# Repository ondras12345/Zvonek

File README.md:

# Zvonek
A simple circuit for ringing a doorbell by briefly pressing a light switch.

The PCB was designed in EAGLE. It was milled out using a CNC. Because I needed
the PCB to be as small as possible, I had to place some of the components
outside the 1.27mm grid.

A fuse (not shown in the schematic) should be placed in series with the 12V
power line.

## Operation
The circuit is connected to a regular light switch, so that the neon lamp is
lit when the light is lit. The neon lamp is pointed at a LDR, thus forming
an optocoupler. A piece of heatshrink tubing is put over this assembly to
isolate it from ambient light.

The circuit is powered from the 12V DC bell power supply and is isolated from
the mains.

When the light is lit, a timer (about 2 s) starts. If the timer has not
finished yet and the light is already switched off, a MOSFET turns on and
the bell sounds.

```
       1   +-----------+           +---+
switch     |           |           |   |
       0 --+           +-----------+   +-------

       1   +------+                +------+
timer      |      |                |      |
       0 --+      +----------------+      +----

       1                               +---+
bell                                   |   |
       0 ------------------------------+   +---
```

This circuit should not be used with regular light bulbs, because the brief
switch-ons would reduce their lifespan. An LED light should be used instead.

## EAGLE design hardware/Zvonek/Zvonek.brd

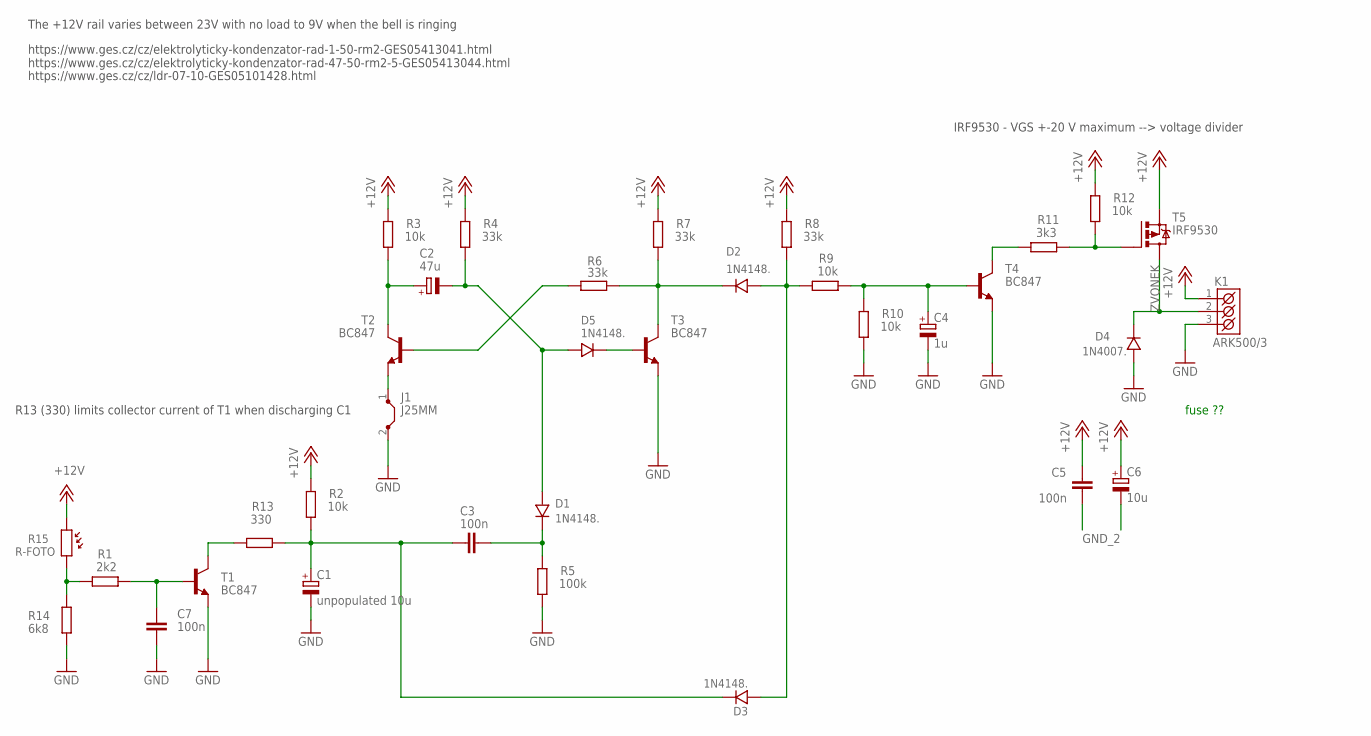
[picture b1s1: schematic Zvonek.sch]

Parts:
C1: unpopulated 10u; E2,5-5
C2: 47u; E2,5-6
C3, C5, C7: 100n; C1206
C4: 1u; E2-5
C6: 10u; E2,5-5
D1, D2, D3, D5: 1N4148.; SOD-80
D4: 1N4007.; SM-1
J1: J25MM; 25
K1: ARK500/3
R1: 2k2; R1206
R2, R3, R9, R10, R12: 10k; R1206
R4, R6, R7, R8: 33k; R1206
R5: 100k; R1206
R11: 3k3; R1206
R13: 330; R1206
R14: 6k8; R1206
R15: R-FOTO
T1, T2, T3, T4: BC847; SOT23
T5: IRF9530; TO220BV

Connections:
+12V: C5.2, C6.+, K1.1 (K1), R2.2, R3.2, R4.2, R7.2, R8.2, R12.2, R15.1, T5.S
GND: C1.-, C4.-, C7.1, D4.A, J1.2, K1.3 (K3), R5.1, R10.1, R14.2, T1.2 (E), T3.2 (E), T4.2 (E)
GND_2: C5.1, C6.-, J1.1, T2.2 (E)
unnamed: D2.K, R6.2, R7.1, T3.3 (C)
unnamed: R6.1, T2.1 (B)
unnamed: C2.-, D1.A, D5.A, R4.1
unnamed: C2.+, R3.1, T2.3 (C)
unnamed: D2.A, D3.A, R8.1, R9.2
unnamed: C3.2, D1.K, R5.2
unnamed: R13.2, T1.3 (C)
unnamed: C7.2, R1.1, T1.1 (B)
unnamed: C4.+, R9.1, R10.2, T4.1 (B)
unnamed: R11.2, T4.3 (C)
unnamed: R11.1, R12.1, T5.G
unnamed: D5.K, T3.1 (B)
unnamed: C1.+, C3.1, D3.K, R2.1, R13.1
unnamed: R1.2, R14.1, R15.2
ZVONEK: D4.K, K1.2 (K2), T5.D

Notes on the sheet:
IRF9530 - VGS +-20 V maximum --> voltage divider
The +12V rail varies between 23V with no load to 9V when the bell is ringing
fuse ??
https://www.ges.cz/cz/elektrolyticky-kondenzator-rad-1-50-rm2-GES05413041.html https://www.ges.cz/cz/elektrolyticky-kondenzator-rad-47-50-rm2-5-GES05413044.html
R13 (330) limits collector current of T1 when discharging C1
https://www.ges.cz/cz/ldr-07-10-GES05101428.html

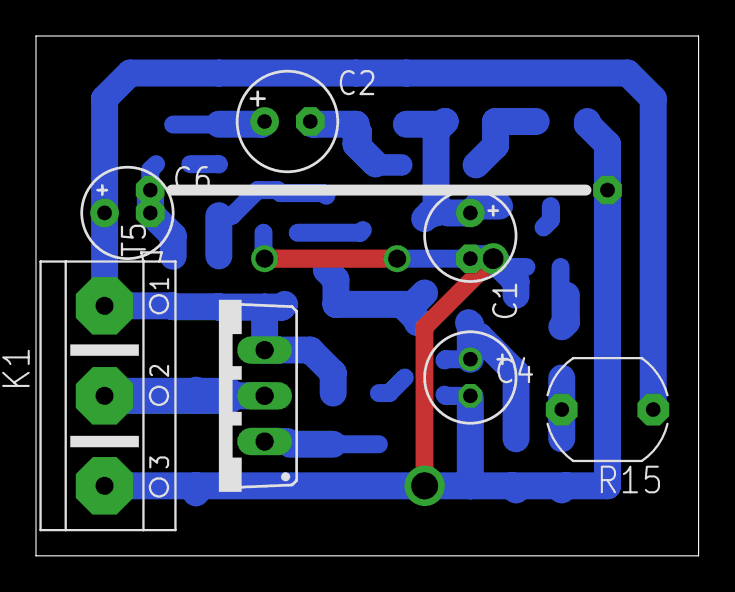
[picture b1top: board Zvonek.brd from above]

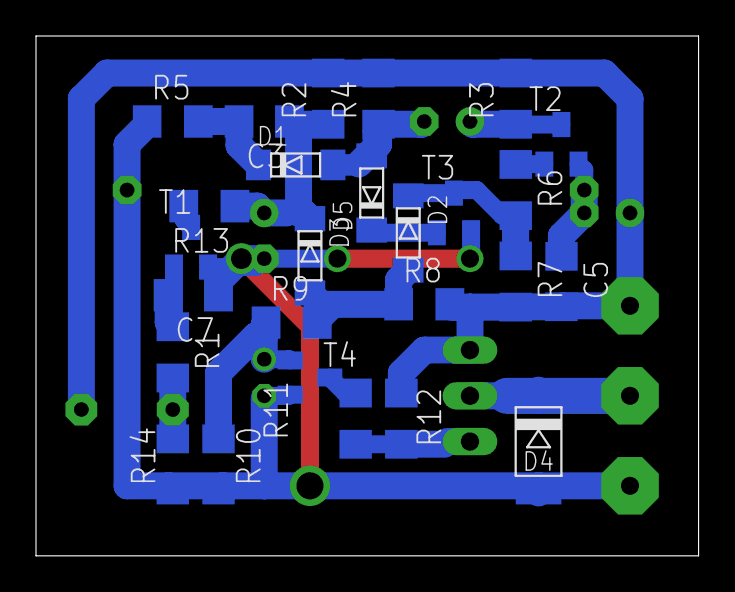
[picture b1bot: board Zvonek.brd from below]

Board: 2 copper layers, 36.8 x 28.9 mm, 34 parts (26 on the bottom side), 18 nets.

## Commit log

2020-06-15 Add .gitignore
2020-06-15 Add project files
    This is the version of the PCB that was actually manufactured.
    (Copper clad only, component values may not match the final product.)
    WARNING: The simulations may not be up to date.
2020-06-15 Add pdf exports
2020-06-15 Change some component values
    This version matches the board that was manufactured.
2020-06-15 Add vim files to .gitignore
2020-06-15 Add README.md
2020-06-15 Add hardware/simulations/README.md

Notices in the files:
parts and their libraries:
Copyright (C) PaJa 2001-2014
Copyright (C) PaJa 2011-2014
